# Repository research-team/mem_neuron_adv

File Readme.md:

Memristive neuron with selectable weights

[Link to a schematic viewer](https://www.altium.com/viewer/)

Weighted spiking neuron idea:

Last version spiking neuron schema: 

Last version of spiking neuron board:

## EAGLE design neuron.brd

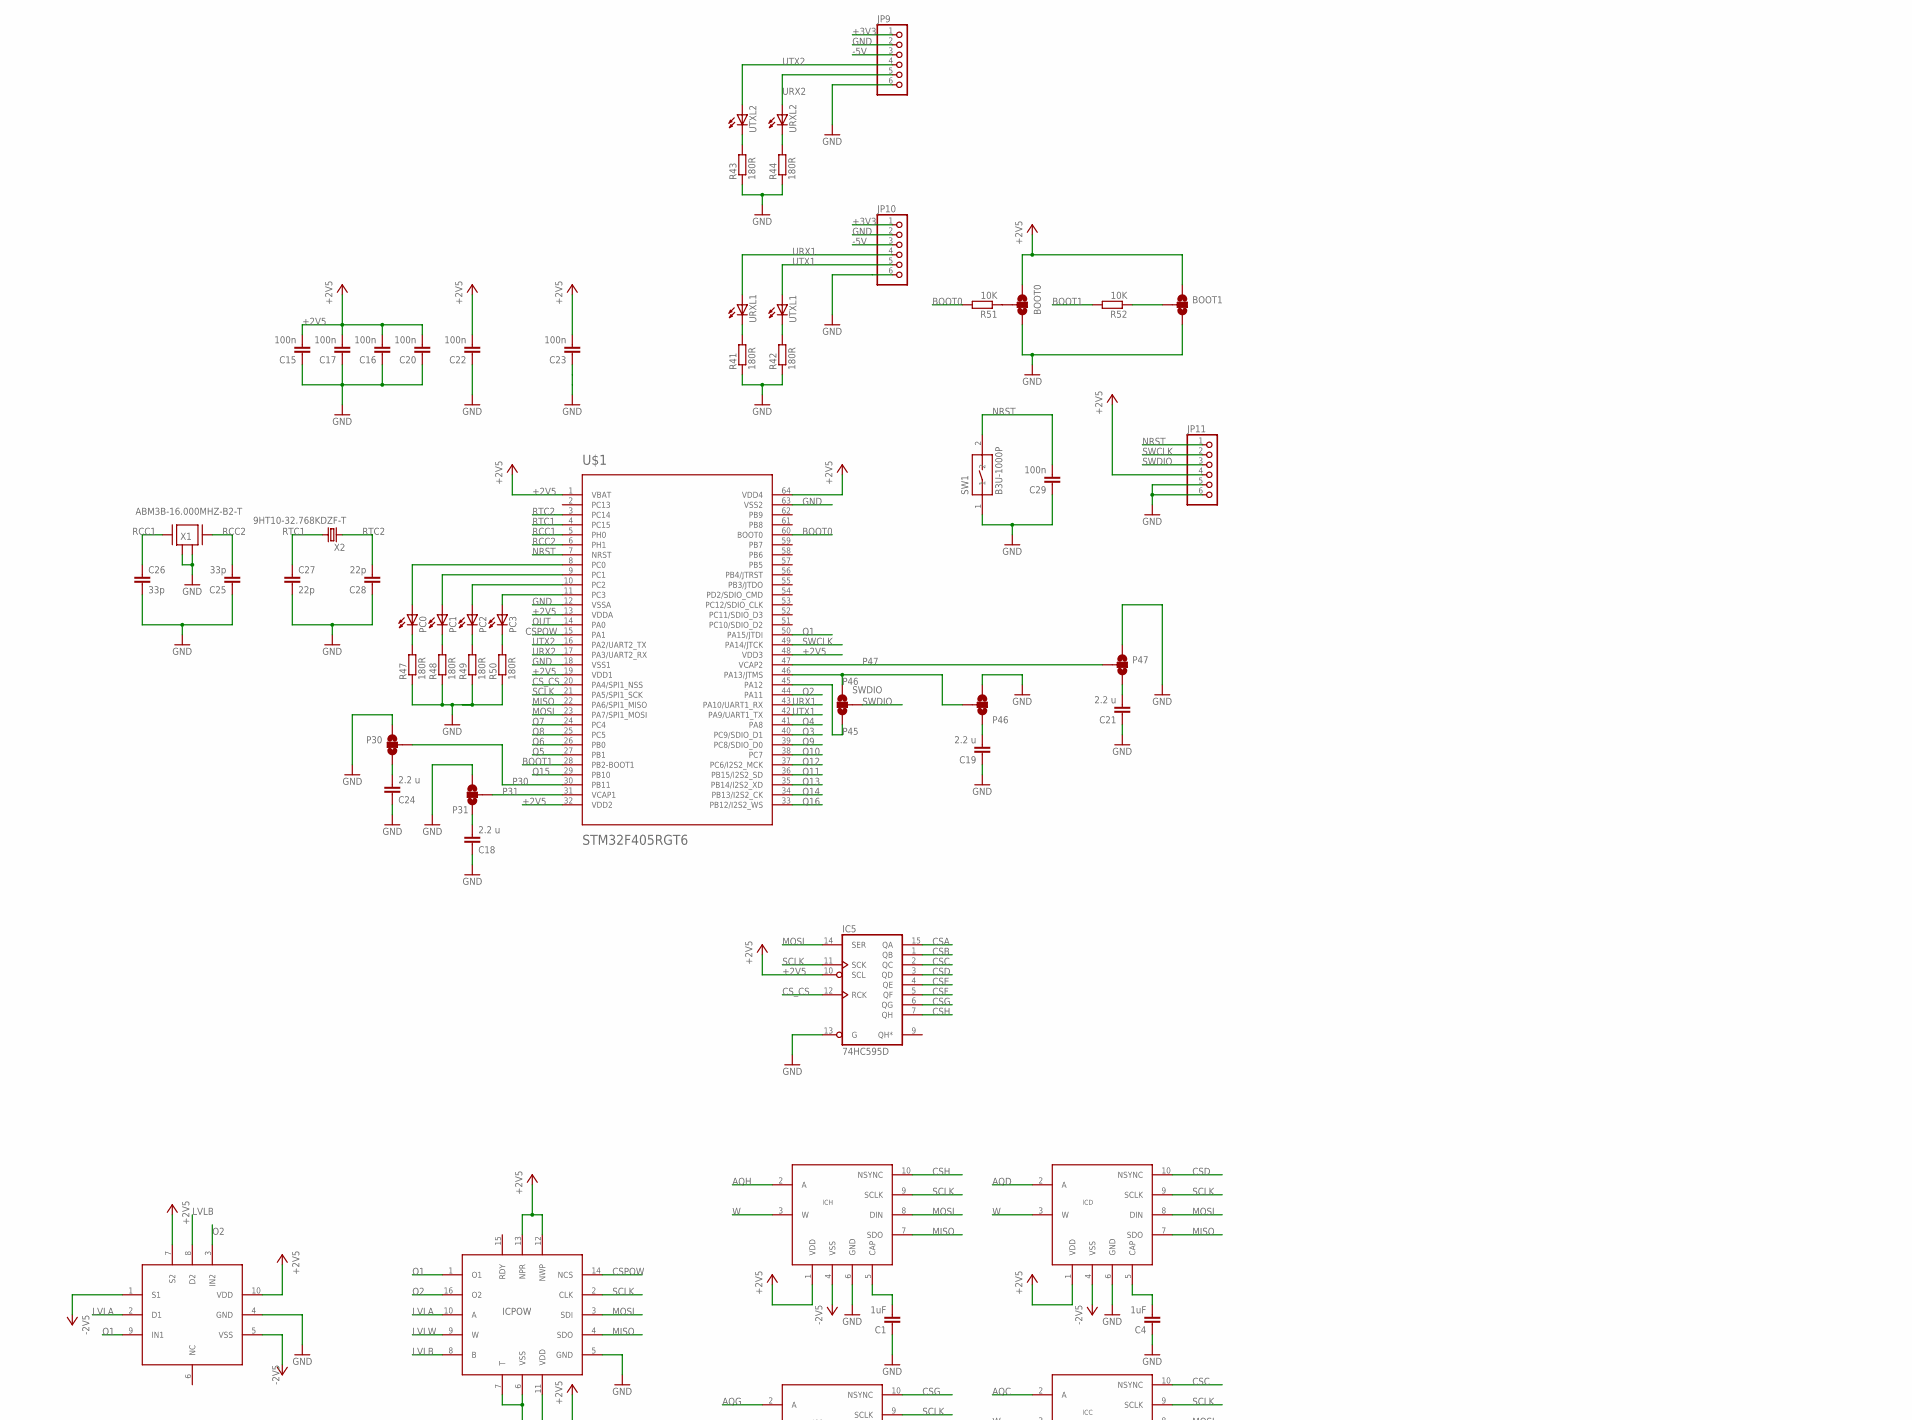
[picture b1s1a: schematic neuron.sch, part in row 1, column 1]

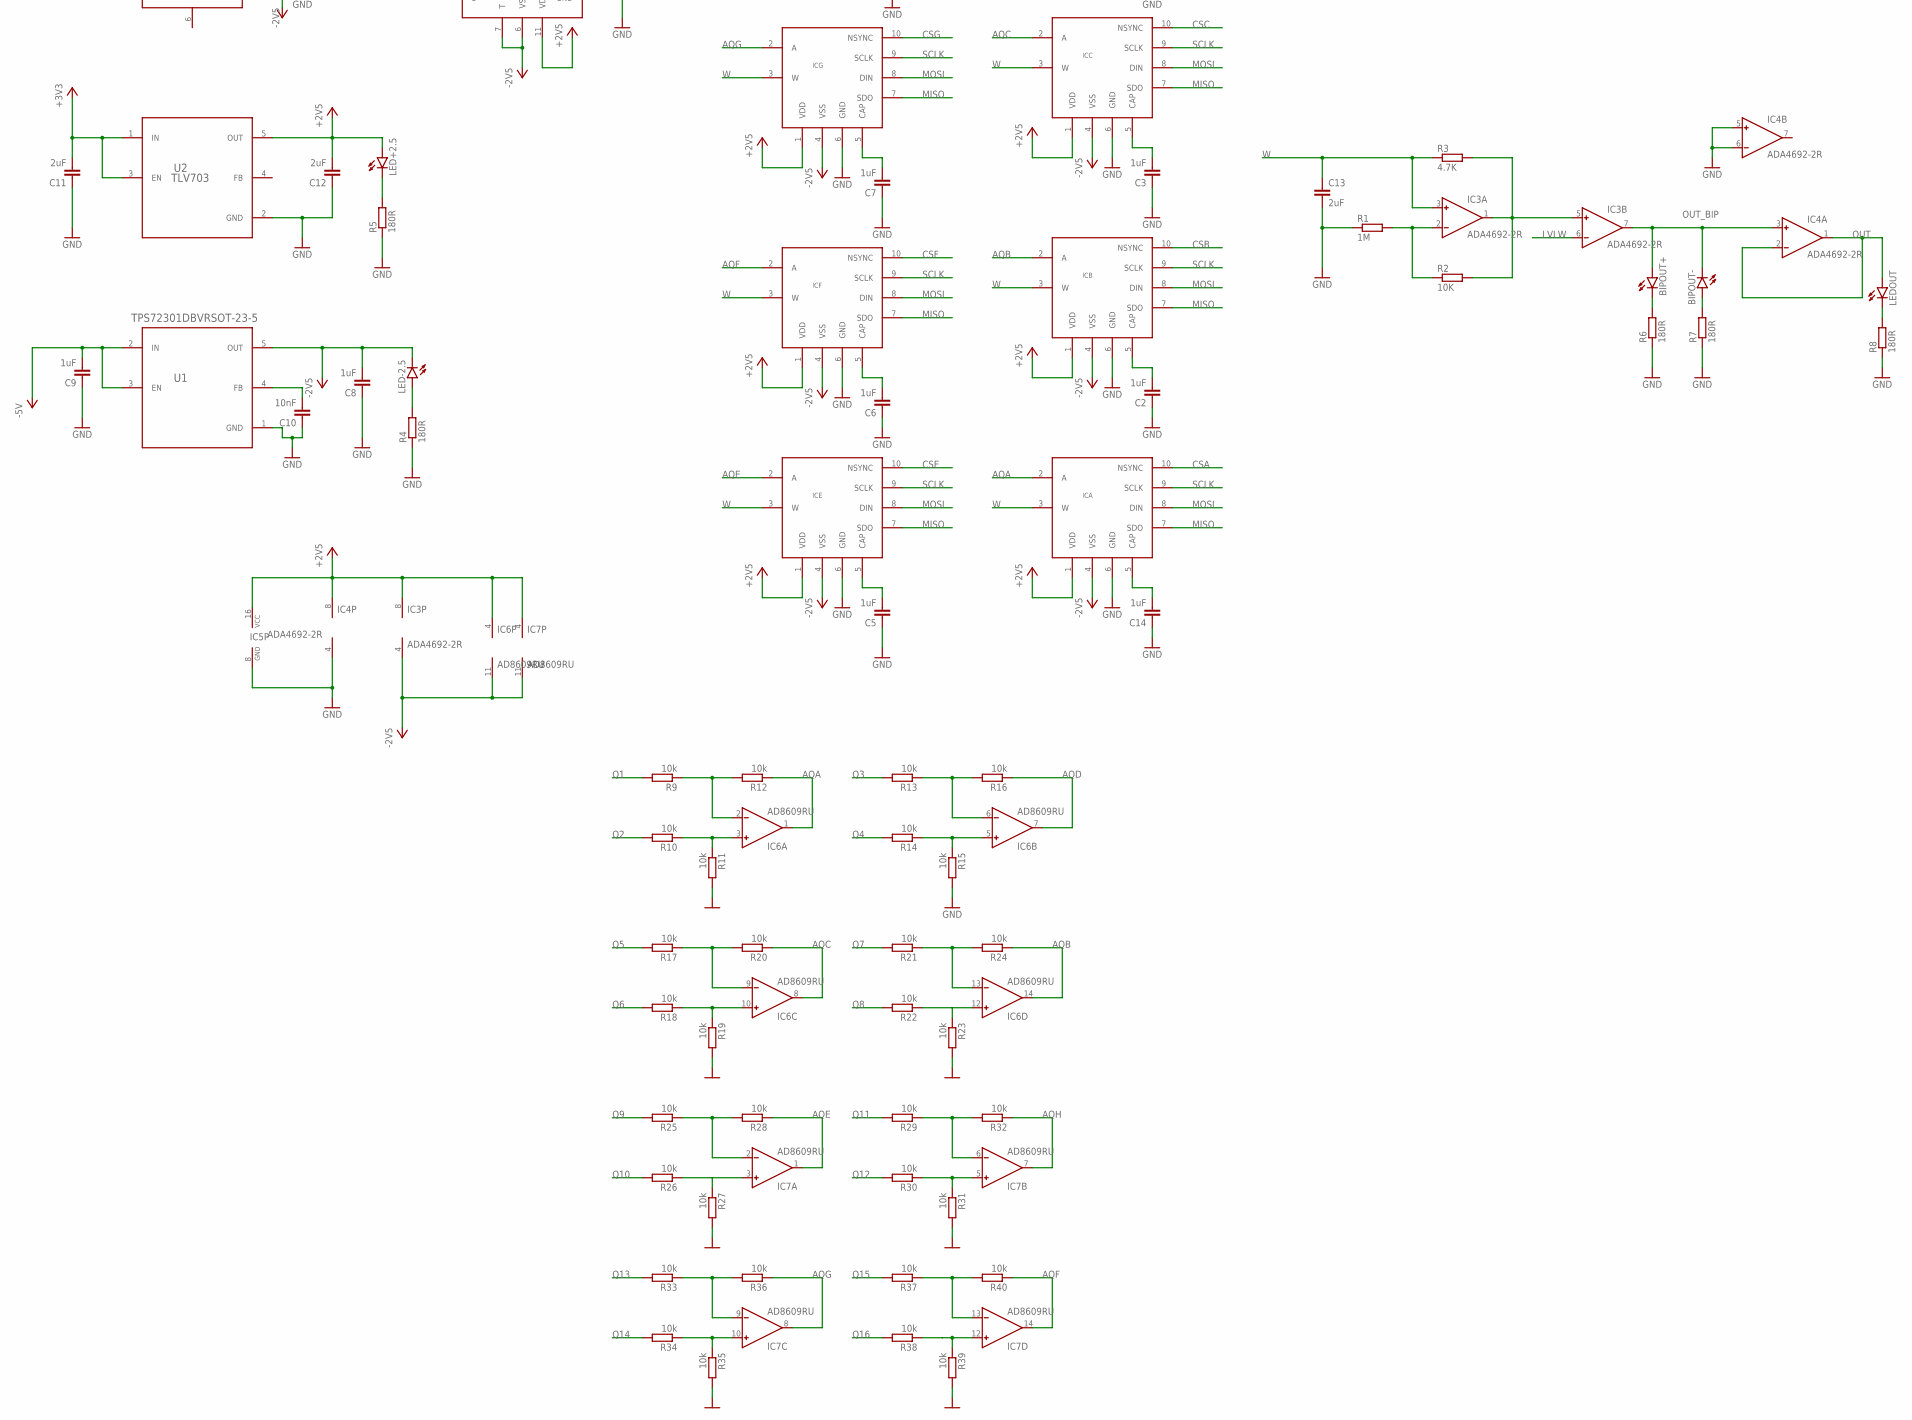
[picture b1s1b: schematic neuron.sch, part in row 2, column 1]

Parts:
BIPOUT+: LEDCHIPLED_0805; CHIPLED_0805
BIPOUT-: LEDCHIPLED_0805; CHIPLED_0805
BOOT0, BOOT1: JUMPER-SMT_3_NO_NO-SILK; SMT-JUMPER_3_NO_NO-SILK
C1, C2, C3, C4, C5, C6, C7, C8, C9, C14: 1uF; C0603
C10: 10nF; C0603
C11, C12: 2uF; C0603
C13: 2uF; C0603K
C15, C16, C17, C20, C22, C23, C29: 100n; C0603K
C18, C19, C21, C24: 2.2 u; C0603K
C25, C26: 33p; C0603K
C27, C28: 22p; C0603K
IC3, IC4: ADA4692-2R; SO8
IC5: 74HC595D; SO16
IC6, IC7: AD8609RU; TSSOP14
ICA: AD5270MSOP10; MSOP10
ICB: AD5270MSOP10; MSOP10
ICC: AD5270MSOP10; MSOP10
ICD: AD5270MSOP10; MSOP10
ICE: AD5270MSOP10; MSOP10
ICF: AD5270MSOP10; MSOP10
ICG: AD5270MSOP10; MSOP10
ICH: AD5270MSOP10; MSOP10
ICPOW: AD5231; TSSOP16
ICSW: ADG621; MSOP10
JP9, JP10, JP11: PINHD-1X6; 1X06
LED+2.5: LEDCHIPLED_0805; CHIPLED_0805
LED-2.5: LEDCHIPLED_0805; CHIPLED_0805
LEDOUT: LEDCHIPLED_0805; CHIPLED_0805
P30, P31, P46, P47: JUMPER-SMT_3_NO_NO-SILK; SMT-JUMPER_3_NO_NO-SILK
PC0, PC1, PC2, PC3: LEDCHIPLED_0805; CHIPLED_0805
R1: 1M; R0603
R2, R51, R52: 10K; R0603
R3: 4.7K; R0603
R4, R5, R6, R7, R8, R41, R42, R43, R44, R47, R48, R49, R50: 180R; R0603
R9, R10, R11, R12, R13, R14, R15, R16, R17, R18, R19, R20, R21, R22, R23, R24, R25, R26, R27, R28, R29, R30, R31, R32, R33, R34, R35, R36, R37, R38, R39, R40: 10k; R0603
SW1: B3U-1000P
SWDIO: JUMPER-SMT_3_NO_NO-SILK; SMT-JUMPER_3_NO_NO-SILK
U1: TPS72301DBVRSOT-23-5; SOT95P280X145-5N
U2: TLV703; SOT95P280X145-5N
U$1: STM32F405RGT6; TQFP64
URXL1, URXL2: LEDCHIPLED_0805; CHIPLED_0805
UTXL1, UTXL2: LEDCHIPLED_0805; CHIPLED_0805
X1: ABM3B-16.000MHZ-B2-T
X2: 9HT10-32.768KDZF-T

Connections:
+2V5: BOOT0.1, BOOT1.1, C12.2, C15.2, C16.2, C17.2, C20.2, C22.2, C23.2, IC3.8 (V+), IC4.8 (V+), IC5.10 (SCL), IC5.16 (VCC), IC6.4 (V+), IC7.4 (V+), ICA.1 (VDD), ICB.1 (VDD), ICC.1 (VDD), ICD.1 (VDD), ICE.1 (VDD), ICF.1 (VDD), ICG.1 (VDD), ICH.1 (VDD), ICPOW.11 (VDD), ICPOW.12 (NWP), ICPOW.13 (NPR), ICSW.7 (S2), ICSW.10 (VDD), JP11.4, LED+2.5.A, U2.5 (OUT), U$1.1 (VBAT), U$1.13 (VDDA), U$1.19 (VDD1), U$1.32 (VDD2), U$1.48 (VDD3), U$1.64 (VDD4)
+3V3: C11.2, JP9.1, JP10.1, U2.1 (IN), U2.3 (EN)
-2V5: C8.2, IC3.4 (V-), IC6.11 (V-), IC7.11 (V-), ICA.4 (VSS), ICB.4 (VSS), ICC.4 (VSS), ICD.4 (VSS), ICE.4 (VSS), ICF.4 (VSS), ICG.4 (VSS), ICH.4 (VSS), ICPOW.6 (VSS), ICPOW.7 (T), ICSW.1 (S1), ICSW.5 (VSS), LED-2.5.C, U1.5 (OUT)
-5V: C9.2, JP9.3, JP10.3, U1.2 (IN), U1.3 (EN)
AQA: IC6.1 (OUT), ICA.2 (A), R12.1
AQB: IC6.14 (OUT), ICB.2 (A), R24.1
AQC: IC6.8 (OUT), ICC.2 (A), R20.1
AQD: IC6.7 (OUT), ICD.2 (A), R16.1
AQE: IC7.1 (OUT), ICE.2 (A), R28.1
AQF: IC7.14 (OUT), ICF.2 (A), R40.1
AQG: IC7.8 (OUT), ICG.2 (A), R36.1
AQH: IC7.7 (OUT), ICH.2 (A), R32.1
BOOT0: R51.2, U$1.60 (BOOT0)
BOOT1: R52.2, U$1.28 (PB2-BOOT1)
CSA: IC5.15 (QA), ICA.10 (NSYNC)
CSB: IC5.1 (QB), ICB.10 (NSYNC)
CSC: IC5.2 (QC), ICC.10 (NSYNC)
CSD: IC5.3 (QD), ICD.10 (NSYNC)
CSE: IC5.4 (QE), ICE.10 (NSYNC)
CSF: IC5.5 (QF), ICF.10 (NSYNC)
CSG: IC5.6 (QG), ICG.10 (NSYNC)
CSH: IC5.7 (QH), ICH.10 (NSYNC)
CSPOW: ICPOW.14 (NCS), U$1.15 (PA1)
CS_CS: IC5.12 (RCK), U$1.20 (PA4/SPI1_NSS)
GND: BOOT0.3, BOOT1.3, C1.1, C2.1, C3.1, C4.1, C5.1, C6.1, C7.1, C8.1, C9.1, C10.1, C11.1, C12.1, C13.2, C14.1, C15.1, C16.1, C17.1, C18.1, C19.1, C20.1, C21.1, C22.1, C23.1, C24.1, C25.1, C26.2, C27.2, C28.1, C29.1, IC4.4 (V-), IC4.5 (IN+), IC4.6 (IN-), IC5.8 (GND), IC5.13 (G), ICA.6 (GND), ICB.6 (GND), ICC.6 (GND), ICD.6 (GND), ICE.6 (GND), ICF.6 (GND), ICG.6 (GND), ICH.6 (GND), ICPOW.5 (GND), ICSW.4 (GND), JP9.2, JP9.6, JP10.2, JP10.6, JP11.5, JP11.6, P30.1, P31.1, P46.1, P47.1, R1.1, R4.1, R5.1, R6.1, R7.1, R8.1, R11.2, R15.2, R19.2, R23.2, R27.2, R31.2, R35.2, R39.2, R41.1, R42.1, R43.1, R44.1, R47.1, R48.1, R49.1, R50.1, SW1.1, U1.1 (GND), U2.2 (GND), U$1.12 (VSSA), U$1.18 (VSS1), U$1.63 (VSS2), X1.2, X1.4
LVLA: ICPOW.10 (A), ICSW.2 (D1)
LVLB: ICPOW.8 (B), ICSW.8 (D2)
LVLW: IC3.6 (IN-), ICPOW.9 (W)
MISO: ICA.7 (SDO), ICB.7 (SDO), ICC.7 (SDO), ICD.7 (SDO), ICE.7 (SDO), ICF.7 (SDO), ICG.7 (SDO), ICH.7 (SDO), ICPOW.4 (SDO), U$1.22 (PA6/SPI1_MISO)
MOSI: IC5.14 (SER), ICA.8 (DIN), ICB.8 (DIN), ICC.8 (DIN), ICD.8 (DIN), ICE.8 (DIN), ICF.8 (DIN), ICG.8 (DIN), ICH.8 (DIN), ICPOW.3 (SDI), U$1.23 (PA7/SPI1_MOSI)
unnamed: C10.2, U1.4 (FB)
unnamed: IC3.1 (OUT), IC3.5 (IN+), R2.2, R3.2
unnamed: C2.2, ICB.5 (CAP)
unnamed: LED-2.5.A, R4.2
unnamed: C1.2, ICH.5 (CAP)
unnamed: IC3.2 (IN-), R1.2, R2.1
unnamed: LED+2.5.C, R5.2
unnamed: C3.2, ICC.5 (CAP)
unnamed: BIPOUT+.C, R6.2
unnamed: BIPOUT-.A, R7.2
unnamed: C4.2, ICD.5 (CAP)
unnamed: LEDOUT.C, R8.2
unnamed: C14.2, ICA.5 (CAP)
unnamed: C5.2, ICE.5 (CAP)
unnamed: IC6.3 (IN+), R10.1, R11.1
unnamed: IC6.6 (IN-), R13.1, R16.2
unnamed: C6.2, ICF.5 (CAP)
unnamed: IC6.10 (IN+), R18.1, R19.1
unnamed: IC6.9 (IN-), R17.1, R20.2
unnamed: C7.2, ICG.5 (CAP)
unnamed: IC6.2 (IN-), R9.1, R12.2
unnamed: IC6.12 (IN+), R22.1, R23.1
unnamed: IC6.13 (IN-), R21.1, R24.2
unnamed: IC7.3 (IN+), R26.1, R27.1
unnamed: IC7.12 (IN+), R38.1, R39.1
unnamed: IC6.5 (IN+), R14.1, R15.1
unnamed: IC7.6 (IN-), R29.1, R32.2
unnamed: IC7.10 (IN+), R34.1, R35.1
unnamed: IC7.9 (IN-), R33.1, R36.2
unnamed: BOOT0.2, R51.1
unnamed: IC7.13 (IN-), R37.1, R40.2
unnamed: IC7.5 (IN+), R30.1, R31.1
unnamed: R43.2, UTXL2.C
unnamed: R44.2, URXL2.C
unnamed: C21.2, P47.3
unnamed: C18.2, P31.3
unnamed: R41.2, URXL1.C
unnamed: R42.2, UTXL1.C
unnamed: IC7.2 (IN-), R25.1, R28.2
unnamed: PC0.C, R47.2
unnamed: PC1.C, R48.2
unnamed: PC2.C, R49.2
unnamed: PC3.C, R50.2
unnamed: C19.2, P46.3
unnamed: BOOT1.2, R52.1
unnamed: C24.2, P30.3
unnamed: PC3.A, U$1.11 (PC3)
unnamed: PC2.A, U$1.10 (PC2)
unnamed: PC1.A, U$1.9 (PC1)
unnamed: PC0.A, U$1.8 (PC0)
NRST: C29.2, JP11.1, SW1.2, U$1.7 (NRST)
O1: ICPOW.1 (O1), ICSW.9 (IN1)
O2: ICPOW.16 (O2), ICSW.3 (IN2)
OUT: IC4.1 (OUT), IC4.2 (IN-), LEDOUT.A, U$1.14 (PA0)
OUT_BIP: BIPOUT+.A, BIPOUT-.C, IC3.7 (OUT), IC4.3 (IN+)
P30: P30.2, U$1.30 (PB11)
P31: P31.2, U$1.31 (VCAP1)
P45: SWDIO.1, U$1.45 (PA12)
P46: P46.2, SWDIO.3, U$1.46 (PA13/JTMS)
P47: P47.2, U$1.47 (VCAP2)
Q1: R9.2, U$1.50 (PA15/JTDI)
Q2: R10.2, U$1.44 (PA11)
Q3: R13.2, U$1.40 (PC9/SDIO_D1)
Q4: R14.2, U$1.41 (PA8)
Q5: R17.2, U$1.27 (PB1)
Q6: R18.2, U$1.26 (PB0)
Q7: R21.2, U$1.24 (PC4)
Q8: R22.2, U$1.25 (PC5)
Q9: R25.2, U$1.39 (PC8/SDIO_D0)
Q10: R26.2, U$1.38 (PC7)
Q11: R29.2, U$1.36 (PB15/I2S2_SD)
Q12: R30.2, U$1.37 (PC6/I2S2_MCK)
Q13: R33.2, U$1.35 (PB14/I2S2_XD)
Q14: R34.2, U$1.34 (PB13/I2S2_CK)
Q15: R37.2, U$1.29 (PB10)
Q16: R38.2, U$1.33 (PB12/I2S2_WS)
RCC1: C26.1, U$1.5 (PH0), X1.1
RCC2: C25.2, U$1.6 (PH1), X1.3
RTC1: C27.1, U$1.4 (PC15), X2.2
RTC2: C28.2, U$1.3 (PC14), X2.1
SCLK: IC5.11 (SCK), ICA.9 (SCLK), ICB.9 (SCLK), ICC.9 (SCLK), ICD.9 (SCLK), ICE.9 (SCLK), ICF.9 (SCLK), ICG.9 (SCLK), ICH.9 (SCLK), ICPOW.2 (CLK), U$1.21 (PA5/SPI1_SCK)
SWCLK: JP11.2, U$1.49 (PA14/JTCK)
SWDIO: JP11.3, SWDIO.2
URX1: JP10.4, U$1.43 (PA10/UART1_RX), URXL1.A
URX2: JP9.5, U$1.17 (PA3/UART2_RX), URXL2.A
UTX1: JP10.5, U$1.42 (PA9/UART1_TX), UTXL1.A
UTX2: JP9.4, U$1.16 (PA2/UART2_TX), UTXL2.A
W: C13.1, IC3.3 (IN+), ICA.3 (W), ICB.3 (W), ICC.3 (W), ICD.3 (W), ICE.3 (W), ICF.3 (W), ICG.3 (W), ICH.3 (W), R3.1

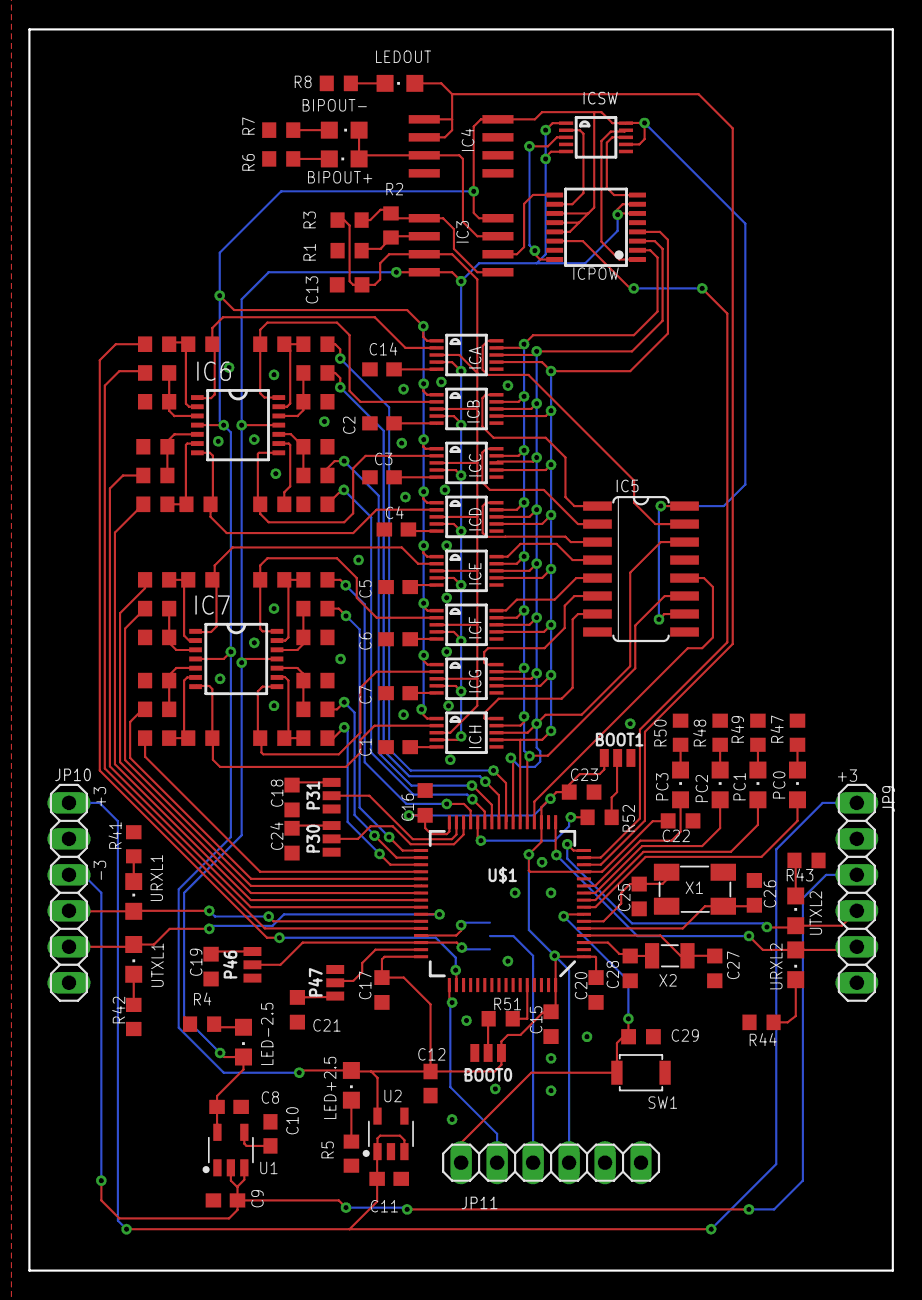
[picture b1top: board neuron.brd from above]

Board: 2 copper layers, 61.0 x 87.6 mm, 123 parts (1 on the bottom side), 118 nets.

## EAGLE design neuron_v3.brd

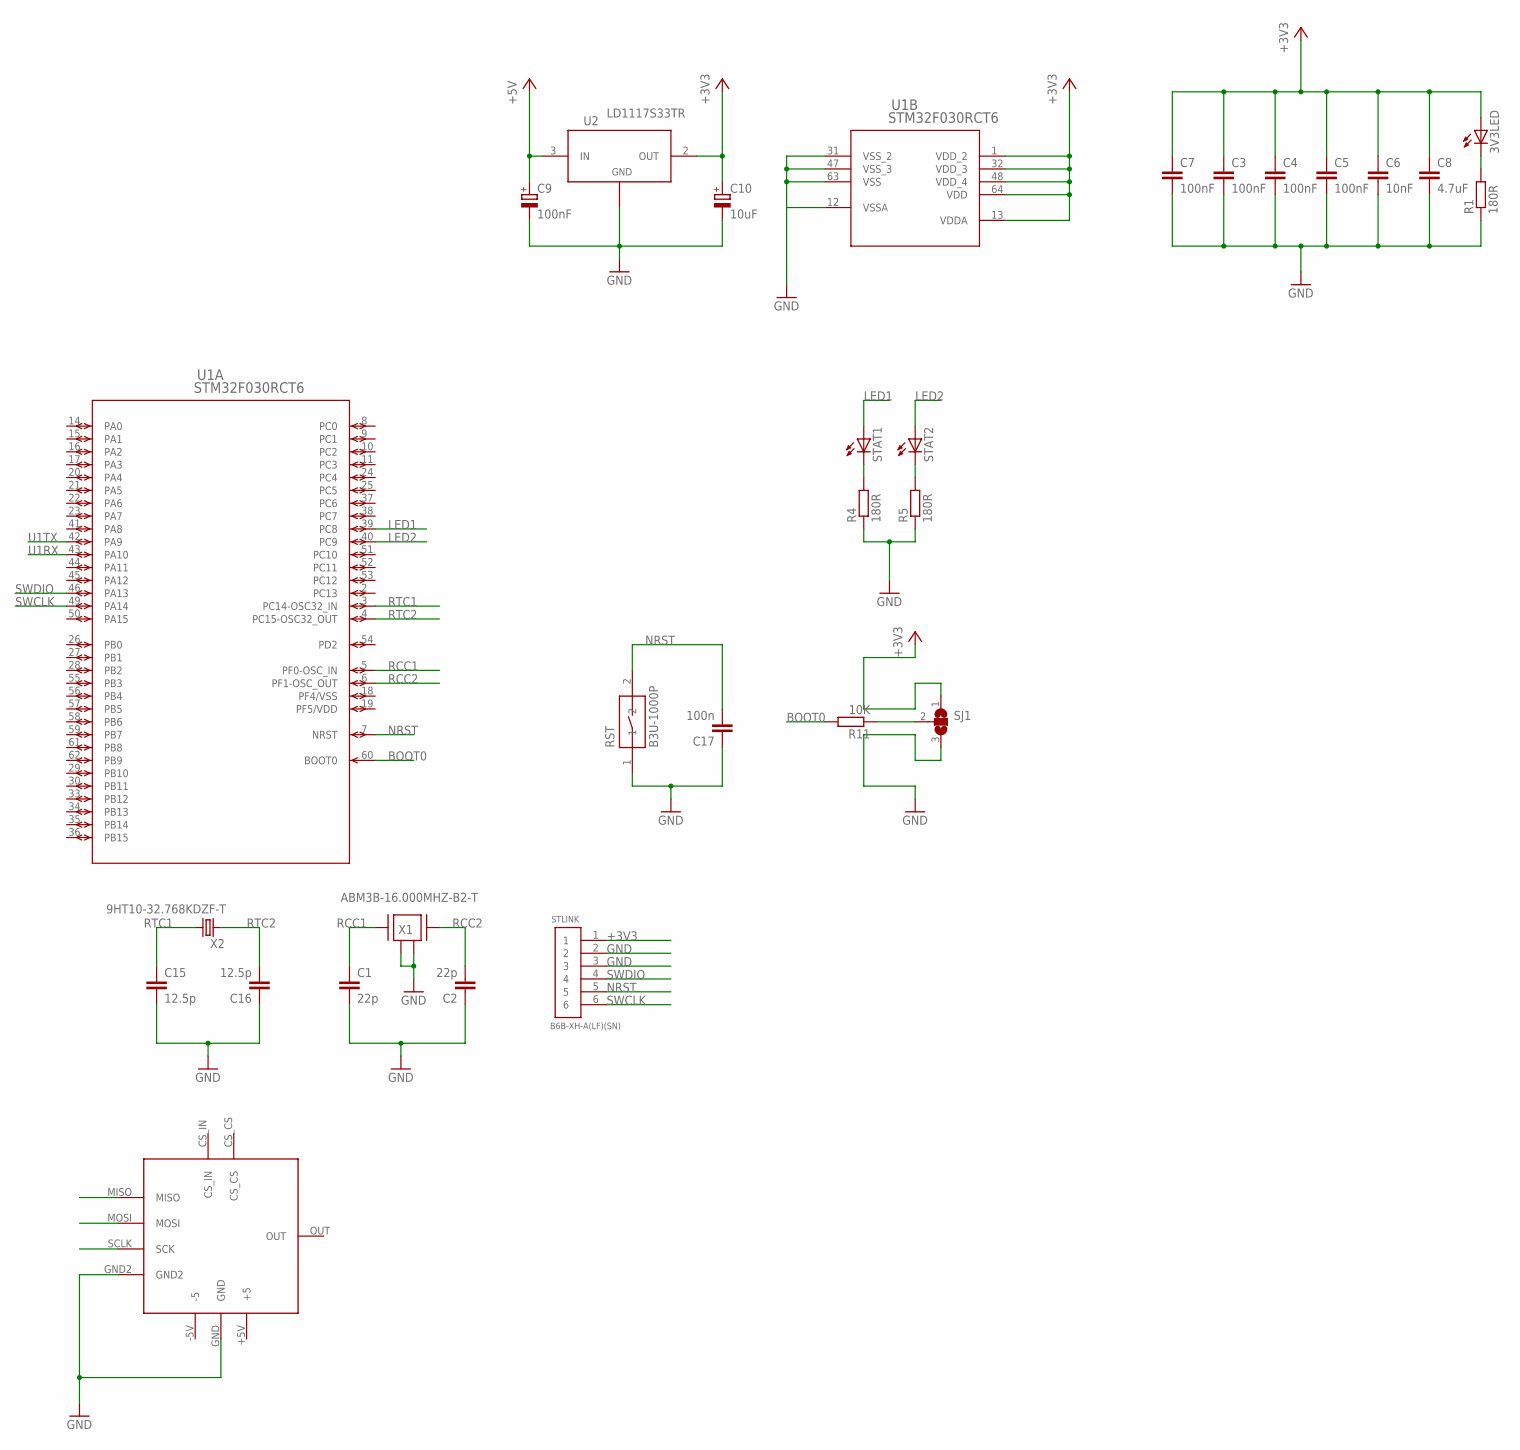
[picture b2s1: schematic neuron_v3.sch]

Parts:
3V3LED: LEDCHIPLED_0805; CHIPLED_0805
C1, C2: 22p; C0603K
C3, C4, C5, C7: 100nF; C0603K
C6: 10nF; C0603K
C8: 4.7uF; C0603K
C9: 100nF; A/3216-18W
C10: 10uF; A/3216-18W
C15, C16: 12.5p; C0603K
C17: 100n; C0603K
R1, R4, R5: 180R; R0603
R11: 10K; R0603
RST: B3U-1000P
SJ1: SJ2W; SJ_2
STAT1, STAT2: LEDCHIPLED_0805; CHIPLED_0805
STLINK: B6B-XH-A(LF)(SN)
U1: STM32F030RCT6; LQFP64-10X10MM
U2: LD1117S33TR; SOT-223
U$1: NEURON_BOARD
X1: ABM3B-16.000MHZ-B2-T
X2: 9HT10-32.768KDZF-T

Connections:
+3V3: 3V3LED.A, C3.1, C4.1, C5.1, C6.1, C7.1, C8.1, C10.+, SJ1.1, STLINK.1, U1.1 (VDD_2), U1.13 (VDDA), U1.32 (VDD_3), U1.48 (VDD_4), U1.64 (VDD), U2.2 (OUT), U2.4
+5V: C9.+, U2.3 (IN)
BOOT0: R11.2, U1.60 (BOOT0)
GND: C1.2, C2.1, C3.2, C4.2, C5.2, C6.2, C7.2, C8.2, C9.-, C10.-, C15.2, C16.1, C17.1, R1.1, R4.1, R5.1, RST.1, SJ1.3, STLINK.2, STLINK.3, U1.12 (VSSA), U1.31 (VSS_2), U1.47 (VSS_3), U1.63 (VSS), U2.1 (ADJ/GND), U$1.GND, U$1.GND2, X1.2, X1.4
LED1: STAT1.A, U1.39 (PC8)
LED2: STAT2.A, U1.40 (PC9)
unnamed: 3V3LED.C, R1.2
unnamed: R4.2, STAT1.C
unnamed: R5.2, STAT2.C
unnamed: R11.1, SJ1.2
NRST: C17.2, RST.2, STLINK.5, U1.7 (NRST)
RCC1: C1.1, U1.5 (PF0-OSC_IN), X1.1
RCC2: C2.2, U1.6 (PF1-OSC_OUT), X1.3
RTC1: C15.1, U1.3 (PC14-OSC32_IN), X2.2
RTC2: C16.2, U1.4 (PC15-OSC32_OUT), X2.1
SWCLK: STLINK.6, U1.49 (PA14)
SWDIO: STLINK.4, U1.46 (PA13)
U1RX: U1.43 (PA10)
U1TX: U1.42 (PA9)

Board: 2 copper layers, 28 parts (0 on the bottom side), 17 nets, no tracks yet.

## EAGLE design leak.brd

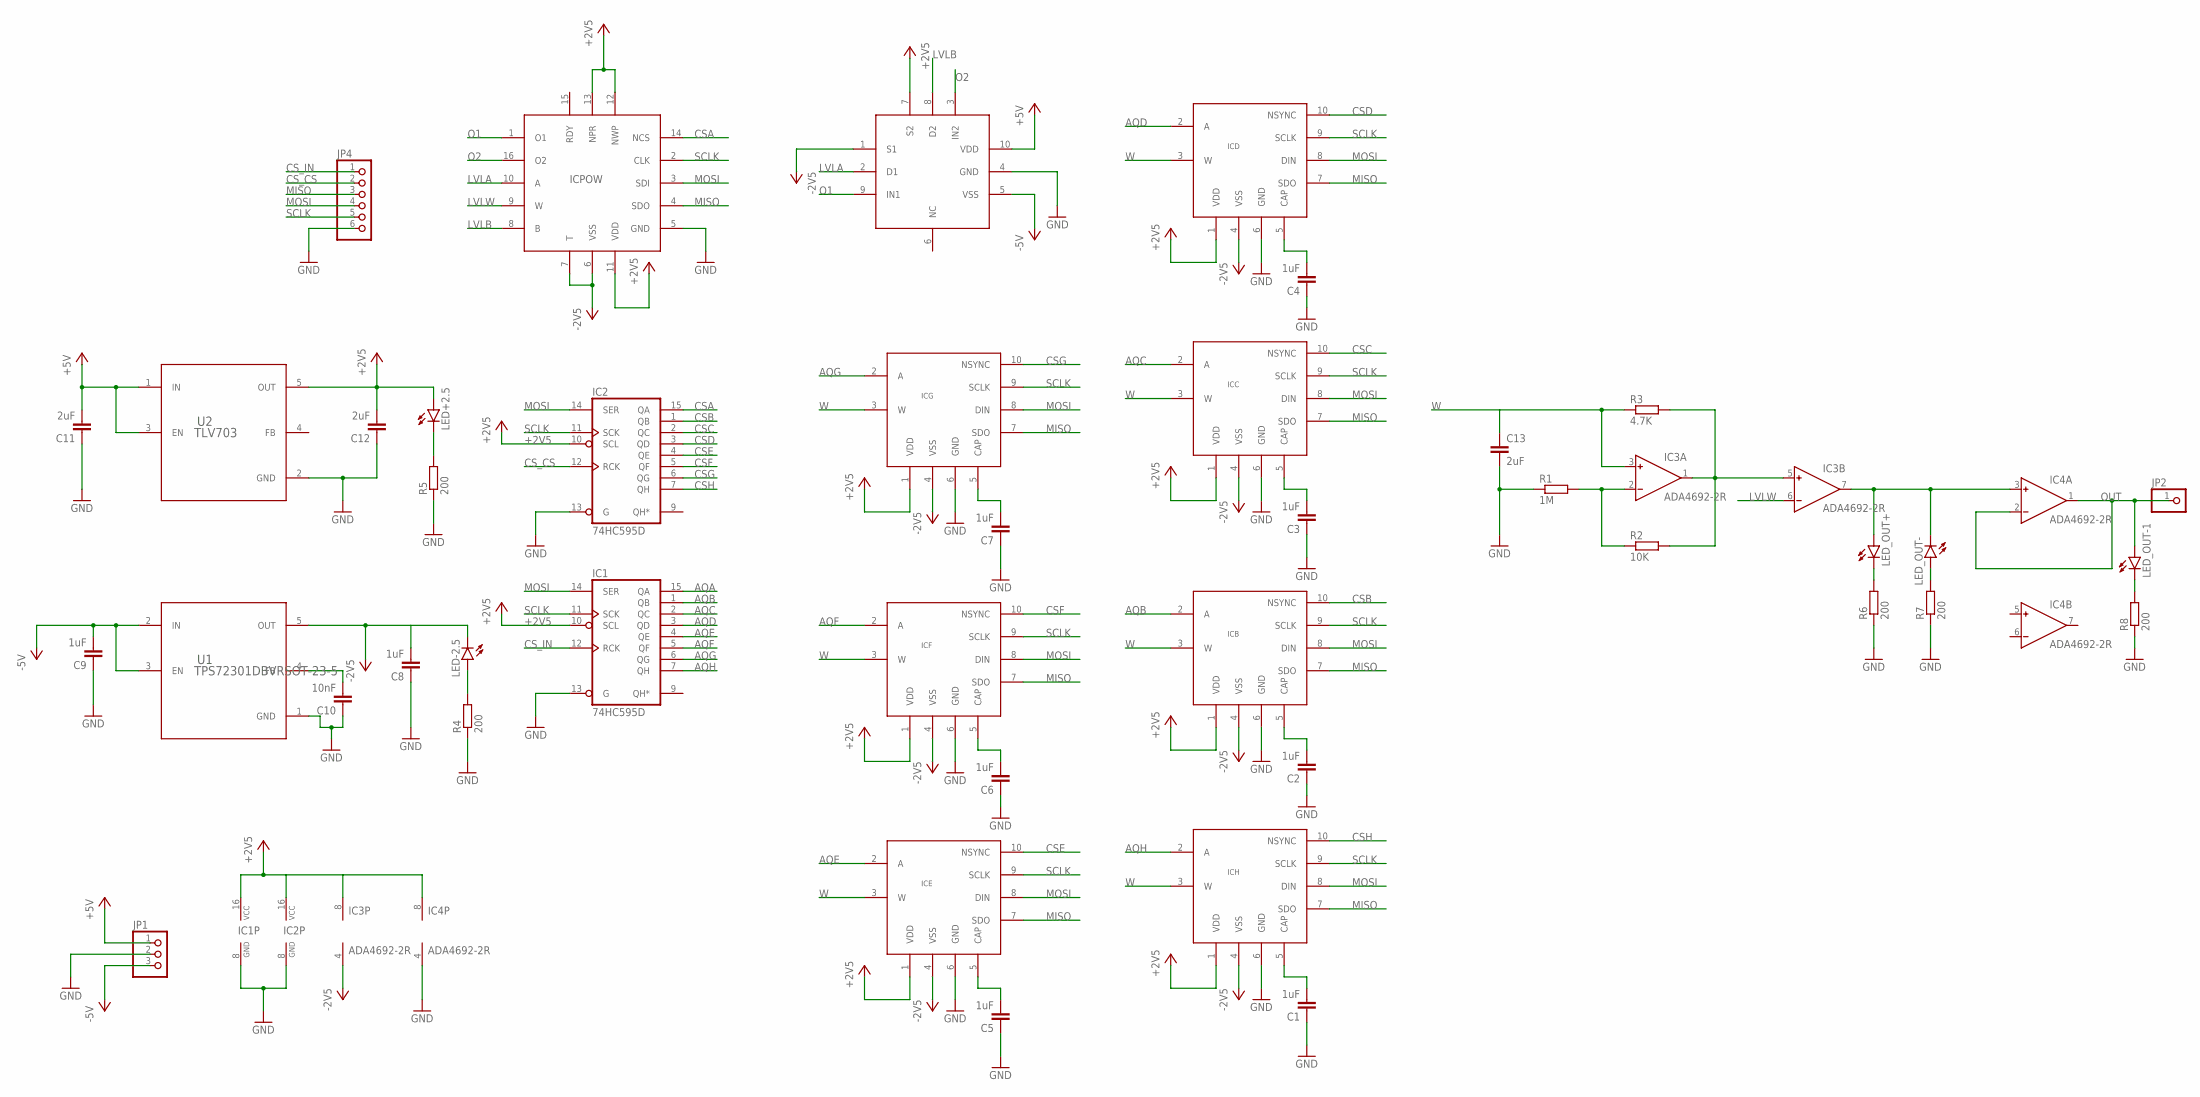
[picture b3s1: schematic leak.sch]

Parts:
C1, C2, C3, C4, C5, C6, C7, C8, C9: 1uF; C0603
C10: 10nF; C0603
C11, C12: 2uF; C0603
C13: 2uF; C0805K
IC1, IC2: 74HC595D; SO16
IC3, IC4: ADA4692-2R; SO8
ICB: AD5270MSOP10; MSOP10
ICC: AD5270MSOP10; MSOP10
ICD: AD5270MSOP10; MSOP10
ICE: AD5270MSOP10; MSOP10
ICF: AD5270MSOP10; MSOP10
ICG: AD5270MSOP10; MSOP10
ICH: AD5270MSOP10; MSOP10
ICPOW: AD5231; TSSOP16
ICSW: ADG621; MSOP10
JP1: PINHD-1X3; 1X03
JP2: PINHD-1X1; 1X01
JP4: PINHD-1X6; 1X06
LED+2.5: LEDCHIPLED_0805; CHIPLED_0805
LED-2.5: LEDCHIPLED_0805; CHIPLED_0805
LED_OUT+: LEDCHIPLED_0805; CHIPLED_0805
LED_OUT-, LED_OUT-1: LEDCHIPLED_0805; CHIPLED_0805
R1: 1M; R0805
R2: 10K; R0805
R3: 4.7K; R0805
R4, R5, R6, R7, R8: 200; R0603
U1: TPS72301DBVRSOT-23-5; SOT95P280X145-5N
U2: TLV703; SOT95P280X145-5N

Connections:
+2V5: C12.2, IC1.10 (SCL), IC1.16 (VCC), IC2.10 (SCL), IC2.16 (VCC), IC3.8 (V+), IC4.8 (V+), ICB.1 (VDD), ICC.1 (VDD), ICD.1 (VDD), ICE.1 (VDD), ICF.1 (VDD), ICG.1 (VDD), ICH.1 (VDD), ICPOW.11 (VDD), ICPOW.12 (NWP), ICPOW.13 (NPR), ICSW.7 (S2), LED+2.5.A, U2.5 (OUT)
+5V: C11.2, ICSW.10 (VDD), JP1.1, U2.1 (IN), U2.3 (EN)
-2V5: C8.2, IC3.4 (V-), ICB.4 (VSS), ICC.4 (VSS), ICD.4 (VSS), ICE.4 (VSS), ICF.4 (VSS), ICG.4 (VSS), ICH.4 (VSS), ICPOW.6 (VSS), ICPOW.7 (T), ICSW.1 (S1), LED-2.5.C, U1.5 (OUT)
-5V: C9.2, ICSW.5 (VSS), JP1.3, U1.2 (IN), U1.3 (EN)
AQA: IC1.15 (QA)
AQB: IC1.1 (QB), ICB.2 (A)
AQC: IC1.2 (QC), ICC.2 (A)
AQD: IC1.3 (QD), ICD.2 (A)
AQE: IC1.4 (QE), ICE.2 (A)
AQF: IC1.5 (QF), ICF.2 (A)
AQG: IC1.6 (QG), ICG.2 (A)
AQH: IC1.7 (QH), ICH.2 (A)
CSA: IC2.15 (QA), ICPOW.14 (NCS)
CSB: IC2.1 (QB), ICB.10 (NSYNC)
CSC: IC2.2 (QC), ICC.10 (NSYNC)
CSD: IC2.3 (QD), ICD.10 (NSYNC)
CSE: IC2.4 (QE), ICE.10 (NSYNC)
CSF: IC2.5 (QF), ICF.10 (NSYNC)
CSG: IC2.6 (QG), ICG.10 (NSYNC)
CSH: IC2.7 (QH), ICH.10 (NSYNC)
CS_CS: IC2.12 (RCK), JP4.2
CS_IN: IC1.12 (RCK), JP4.1
GND: C1.1, C2.1, C3.1, C4.1, C5.1, C6.1, C7.1, C8.1, C9.1, C10.1, C11.1, C12.1, C13.2, IC1.8 (GND), IC1.13 (G), IC2.8 (GND), IC2.13 (G), IC4.4 (V-), ICB.6 (GND), ICC.6 (GND), ICD.6 (GND), ICE.6 (GND), ICF.6 (GND), ICG.6 (GND), ICH.6 (GND), ICPOW.5 (GND), ICSW.4 (GND), JP1.2, JP4.6, R1.1, R4.1, R5.1, R6.1, R7.1, R8.1, U1.1 (GND), U2.2 (GND)
LVLA: ICPOW.10 (A), ICSW.2 (D1)
LVLB: ICPOW.8 (B), ICSW.8 (D2)
LVLW: IC3.6 (IN-), ICPOW.9 (W)
MISO: ICB.7 (SDO), ICC.7 (SDO), ICD.7 (SDO), ICE.7 (SDO), ICF.7 (SDO), ICG.7 (SDO), ICH.7 (SDO), ICPOW.4 (SDO), JP4.3
MOSI: IC1.14 (SER), IC2.14 (SER), ICB.8 (DIN), ICC.8 (DIN), ICD.8 (DIN), ICE.8 (DIN), ICF.8 (DIN), ICG.8 (DIN), ICH.8 (DIN), ICPOW.3 (SDI), JP4.4
unnamed: C10.2, U1.4 (FB)
unnamed: IC3.1 (OUT), IC3.5 (IN+), R2.2, R3.2
unnamed: C2.2, ICB.5 (CAP)
unnamed: LED-2.5.A, R4.2
unnamed: C1.2, ICH.5 (CAP)
unnamed: IC3.2 (IN-), R1.2, R2.1
unnamed: LED+2.5.C, R5.2
unnamed: C3.2, ICC.5 (CAP)
unnamed: LED_OUT+.C, R6.2
unnamed: LED_OUT-.A, R7.2
unnamed: C4.2, ICD.5 (CAP)
unnamed: LED_OUT-1.C, R8.2
unnamed: C5.2, ICE.5 (CAP)
unnamed: C6.2, ICF.5 (CAP)
unnamed: C7.2, ICG.5 (CAP)
O1: ICPOW.1 (O1), ICSW.9 (IN1)
O2: ICPOW.16 (O2), ICSW.3 (IN2)
OUT: IC3.7 (OUT), IC4.1 (OUT), IC4.2 (IN-), IC4.3 (IN+), JP2.1, LED_OUT+.A, LED_OUT-.C, LED_OUT-1.A
SCLK: IC1.11 (SCK), IC2.11 (SCK), ICB.9 (SCLK), ICC.9 (SCLK), ICD.9 (SCLK), ICE.9 (SCLK), ICF.9 (SCLK), ICG.9 (SCLK), ICH.9 (SCLK), ICPOW.2 (CLK), JP4.5
W: C13.1, IC3.3 (IN+), ICB.3 (W), ICC.3 (W), ICD.3 (W), ICE.3 (W), ICF.3 (W), ICG.3 (W), ICH.3 (W), R3.1

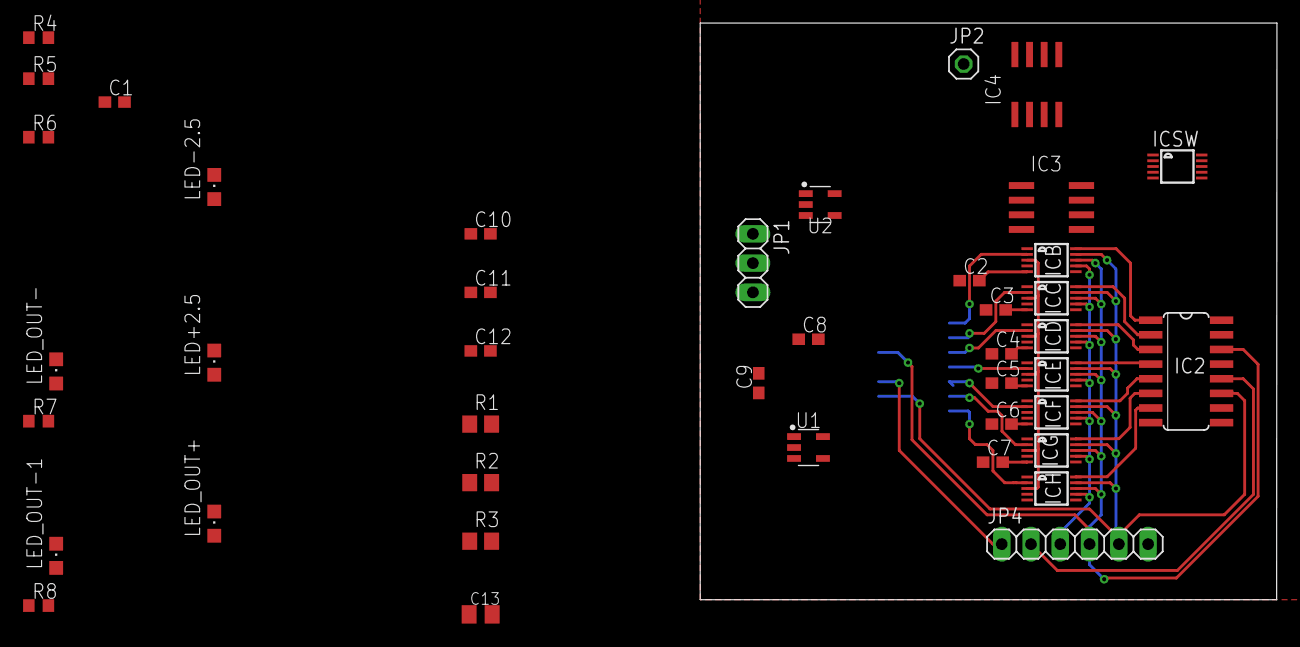
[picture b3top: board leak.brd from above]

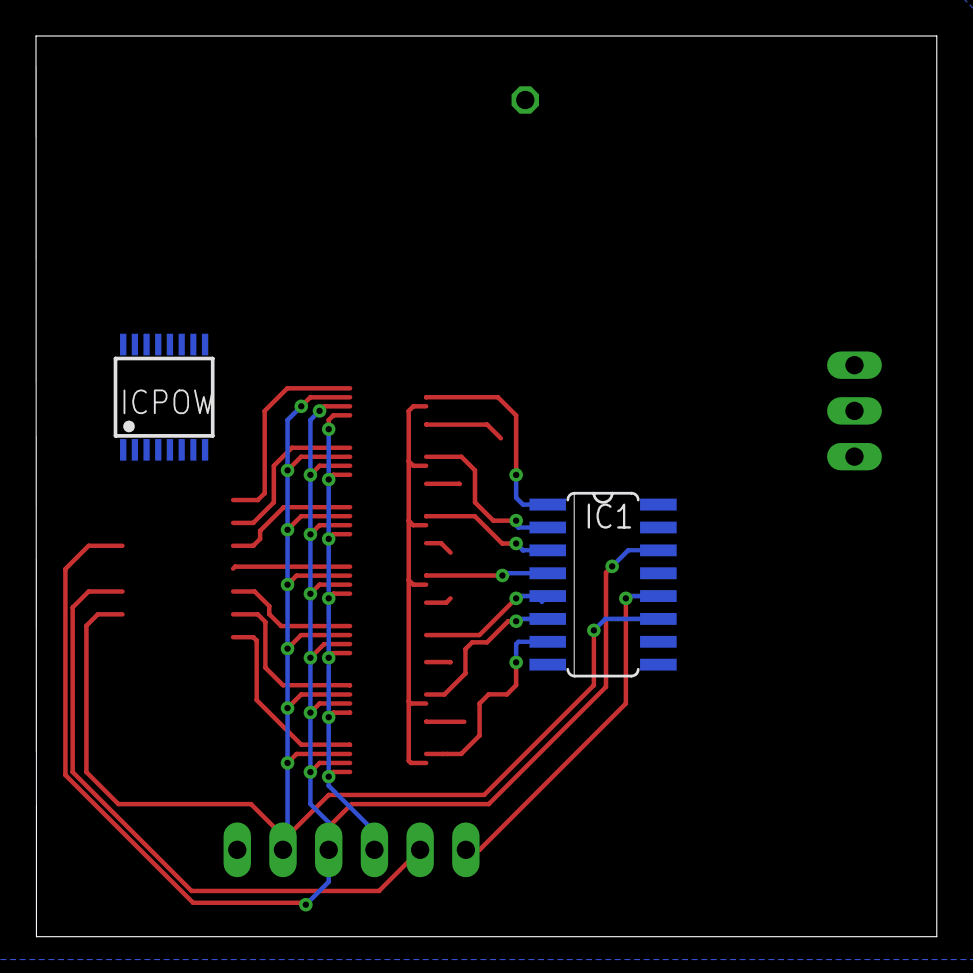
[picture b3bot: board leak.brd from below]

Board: 2 copper layers, 50.0 x 50.0 mm, 44 parts (2 on the bottom side), 47 nets.

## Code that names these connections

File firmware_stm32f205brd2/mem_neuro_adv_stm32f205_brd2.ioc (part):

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PB10.PinState=GPIO_PIN_SET
PB13.GPIOParameters=PinState,GPIO_Label
PA6.Mode=Full_Duplex_Master
PC7.GPIOParameters=PinState,GPIO_Label
PH0-OSC_IN.Signal=RCC_OSC_IN
Mcu.UserName=STM32F205RETx
PC10.Signal=SPI3_SCK
PC12.Signal=SPI3_MOSI
PB14.GPIO_Label=Q13
PC0.GPIOParameters=GPIO_Label
PA11.GPIOParameters=PinState,GPIO_Label
PC6.GPIO_Label=Q12
PC0.GPIO_Label=LED1
PB0.GPIO_Label=Q6
PB13.GPIO_Label=Q14
PB13.Signal=GPIO_Output
PB15.Signal=GPIO_Output
PB15.PinState=GPIO_PIN_SET
RCC.SYSCLKSource=RCC_SYSCLKSOURCE_PLLCLK
PC8.PinState=GPIO_PIN_SET
PA15.GPIO_Label=Q1
PC1.GPIOParameters=GPIO_Label
PB0.PinState=GPIO_PIN_SET
PC7.Signal=GPIO_Output
PB12.PinState=GPIO_PIN_SET
PC3.Signal=GPIO_Output
PA8.GPIOParameters=PinState,GPIO_Label
PH0-OSC_IN.Mode=HSE-External-Oscillator
PA0-WKUP.GPIOParameters=GPIO_PuPd,GPIO_Label
RCC.HSE_VALUE=16000000
PB12.GPIO_Label=Q16
PB0.GPIOParameters=PinState,GPIO_Label
PA1.GPIOParameters=PinState,GPIO_Label
PC4.GPIO_Label=Q7
PA14.Mode=Serial_Wire
PB1.GPIO_Label=Q5
PC7.PinState=GPIO_PIN_SET
PA8.Signal=GPIO_Output
PB1.PinState=GPIO_PIN_SET
PH1-OSC_OUT.Mode=HSE-External-Oscillator
PC8.GPIOParameters=PinState,GPIO_Label
Mcu.Package=LQFP64
PB1.Signal=GPIO_Output
PA6.Signal=SPI1_MISO
PA10.Signal=USART1_RX
PA15.Signal=GPIO_Output
PA1.PinState=GPIO_PIN_SET
PB14.GPIOParameters=PinState,GPIO_Label
PC5.Signal=GPIO_Output
PB10.GPIOParameters=PinState,GPIO_Label
PA4.GPIO_Label=CS_CS
PC2.GPIO_Label=LED3
PC4.GPIOParameters=GPIO_Label
PA8.PinState=GPIO_PIN_SET
PA3.Signal=USART2_RX
PA5.Mode=Full_Duplex_Master
PA7.Mode=Full_Duplex_Master
PA10.Mode=Asynchronous
PA15.GPIOParameters=PinState,GPIO_Label
PC9.GPIO_Label=Q3
PC8.Signal=GPIO_Output
PC2.Signal=GPIO_Output
PC4.Signal=GPIO_Output
PC6.Signal=GPIO_Output
PC10.Mode=TX_Only_Simplex_Unidirect_Master
PC9.PinState=GPIO_PIN_SET
PA11.GPIO_Label=Q2
PC0.Signal=GPIO_Output
PA0-WKUP.GPIO_Label=OUT
PA0-WKUP.Signal=GPXTI0
PC3.GPIOParameters=GPIO_Label
PC8.GPIO_Label=Q9
PA3.Mode=Asynchronous
PA13.Signal=SYS_JTMS-SWDIO
PA9.Mode=Asynchronous
PA8.GPIO_Label=Q4
PB14.PinState=GPIO_PIN_SET
PA4.PinState=GPIO_PIN_SET
PB10.GPIO_Label=Q15
PC5.GPIOParameters=PinState,GPIO_Label
PA9.Signal=USART1_TX
PA1.Signal=GPIO_Output
PB10.Signal=GPIO_Output
PC6.PinState=GPIO_PIN_SET
PB14.Signal=GPIO_Output
PA5.Signal=SPI1_SCK
PC12.Mode=TX_Only_Simplex_Unidirect_Master
board=custom
PA15.PinState=GPIO_PIN_SET
PB13.PinState=GPIO_PIN_SET
PB15.GPIO_Label=Q11
PC2.GPIOParameters=GPIO_Label
PC1.GPIO_Label=LED2
PA1.GPIO_Label=CSPOW
PH1-OSC_OUT.Signal=RCC_OSC_OUT
PA4.GPIOParameters=PinState,GPIO_Label
PB15.GPIOParameters=PinState,GPIO_Label
PA13.Mode=Serial_Wire
PC9.GPIOParameters=PinState,GPIO_Label
Mcu.Name=STM32F205R(B-C-E-F-G)Tx
PA2.Signal=USART2_TX
PC7.GPIO_Label=Q10
PA4.Signal=GPIO_Output
RCC.SYSCLKFreq_VALUE=120000000
PC5.PinState=GPIO_PIN_SET
PC5.GPIO_Label=Q8
PA11.Signal=GPIO_Output
PA14.Signal=SYS_JTCK-SWCLK
PC6.GPIOParameters=PinState,GPIO_Label
PA2.Mode=Asynchronous
PC3.GPIO_Label=LED4
PA0-WKUP.GPIO_PuPd=GPIO_PULLDOWN
PC9.Signal=GPIO_Output
PA11.PinState=GPIO_PIN_SET
PB0.Signal=GPIO_Output
PC1.Signal=GPIO_Output
PB12.GPIOParameters=PinState,GPIO_Label
PB12.Signal=GPIO_Output
PB1.GPIOParameters=PinState,GPIO_Label
PA7.Signal=SPI1_MOSI

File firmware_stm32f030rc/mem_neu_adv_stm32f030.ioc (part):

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Mcu.Name=STM32F030RCTx
Mcu.Package=LQFP64
Mcu.UserName=STM32F030RCTx
PA10.Mode=Asynchronous
PA10.Signal=USART1_RX
PA5.Mode=Full_Duplex_Master
PA5.Signal=SPI1_SCK
PA6.Mode=Full_Duplex_Master
PA6.Signal=SPI1_MISO
PA7.Mode=Full_Duplex_Master
PA7.Signal=SPI1_MOSI
PA9.Mode=Asynchronous
PA9.Signal=USART1_TX
PC14OSC32_IN.Mode=LSE-External-Oscillator
PC14OSC32_IN.Signal=RCC_OSC32_IN
PC15OSC32_OUT.Mode=LSE-External-Oscillator
PC15OSC32_OUT.Signal=RCC_OSC32_OUT
PF0-OSC_IN.Mode=HSE-External-Oscillator
PF0-OSC_IN.Signal=RCC_OSC_IN
PF1-OSC_OUT.Mode=HSE-External-Oscillator
PF1-OSC_OUT.Signal=RCC_OSC_OUT
board=custom

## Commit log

2020-03-18 init
2020-03-20 modifications
2020-03-20 few more connections
2020-03-31 added readme
2020-03-31 added link to a viewer and op amp
2020-03-31 added picture to docs
2020-03-31 finished schematic
2020-04-01 started pcb layout
2020-04-07 v1 finished
2020-04-07 added pictures for v1
2020-04-08 modified filenames to match reality
2020-04-08 fixed links
2020-04-08 fixed tabs
2020-04-08 modified board picture
2020-04-08 more picture modification
2020-04-08 added drawio diagram for idea
2020-04-08 renaming
2020-04-08 added some measurements
2020-04-08 added basics for OM board
2020-04-14 added spiking
2020-06-02 added new version with controller
2020-06-09 Almost finished neuron v2
2021-02-10 finished v1
2021-02-10 some patches
2021-02-10 last push to a360
2021-03-15 added firmware
2021-03-25 added all init
2021-03-31 added some uart tests
2021-04-02 added uart parser
2021-04-14 modified connection
2021-04-15 multiple boards test
2021-04-21 added multiple firmwares
2021-04-21 rdy for 3 neuron
2021-04-26 added some data
2021-04-27 weight resistors fixed
2021-04-27 something made
2021-05-11 some fitting
2021-05-12 added stdp

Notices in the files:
parts and their libraries:
SparkFun-IC-Microcontroller: Licensing: Creative Commons ShareAlike 4.0 International - https://creativecommons.org/licenses/by-sa/4.0
COPYRIGHT: Copyright (C) 2018 Accelerated Designs. All rights reserved
